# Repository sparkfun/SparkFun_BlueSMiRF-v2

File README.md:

# SparkFun BlueSMiRF v2

The [SparkFun BlueSMiRF v2](https://www.sparkfun.com/sparkfun-bluesmirf-v2.html), [SparkFun BlueSMiRF v2 - Headers](https://www.sparkfun.com/sparkfun-bluesmirf-v2-headers.html), and [SparkFun BlueSMiRF v2 - JST](https://www.sparkfun.com/sparkfun-bluesmirf-v2-jst.html) are wireless Bluetooth® serial links. These boards work as a wireless serial UART pipe and are a great wireless replacement for serial cables. Simply pair, connect, and transmit serial data between your TX/RX lines! Any serial stream from 2400 to 921600 baud can be passed seamlessly between two devices.

Duplex transmissions up to 921600bps are supported. What does this mean? You can throw a book at each BlueSMiRF, which will correctly buffer, transmit, and deliver the data streams, byte perfect, to both radios.

BlueSMiRF v2 has a multitude of exciting improvements over the original. The BlueSMiRF pinout is the same as previous Bluetooth Mates and USB-to-serial converters (i.e., FTDI, CH340, etc.), making it extremely easy to hook up to many common Arduino development boards and GNSS breakout boards.  The board can be connected directly with an Arduino Pro, Pro Mini, or any board with a standard 6-pin serial connector. We broke out the pins to the 1x6 header for this version of the board. You'll need to either solder a 1x6 female header or striped wires to the PTHs before being able to connect to another device. The SparkFun BlueSMiRF v2 is perfect for short-range applications up to 100ft (33m) indoors that require easy to setup, point-to-point communication.

A BlueSMiRF can be connected to a phone or computer to view data or remote control easily. Two BlueSMiRFs can also be easily connected using the onboard PAIR button. If needed, this button can be disabled by cutting the jumper on the back of the board.

We've designed the BlueSMiRF to be remotely configured from a phone using a serial terminal app. Changing the settings, such as the baud rate, flow control, and LED mode, is easily done using the simple AT command set. Additionally, Over The Air (OTA) updates using WiFi allow easy in-field firmware updates as new features are released.

The BlueSMiRF v2 has an on-board voltage regulator to power between 3.3V and 5V. Logic level shifting circuitry is included on all pins to be 3.3V to 5V tolerant. Note that you will need an RS232 to TTL converter for higher voltages. A jumper on the top of the board is also included to bypass the voltage regulator. Two built-in LEDs indicate when the BlueSMiRF is connected and when there is serial UART traffic.

> [!NOTE]
> Bluetooth® classic (Serial Port Profile or SPP) is primarily supported. This Bluetooth protocol is supported on Android phones, most desktops, and laptops. BlueSMiRF also supports the BLE protocol, available on all Apple phones.

This repo houses the [BlueSMiRF v2 Hookup Guide](https://docs.sparkfun.com/SparkFun_BlueSMiRF-v2) and the firmware that runs on the SparkFun BlueSMiRF v2 product line including:

- [SparkFun BlueSMiRF v2 - PTH Pins](https://www.sparkfun.com/sparkfun-bluesmirf-v2.html)
- [SparkFun BlueSMiRF v2 - Male Header Pins](https://www.sparkfun.com/sparkfun-bluesmirf-v2-headers.html)
- [SparkFun BlueSMiRF v2 - JST-GH Connector](https://www.sparkfun.com/sparkfun-bluesmirf-v2-jst.html)

> [!NOTE]
> For compiled binaries of the firmware, please see [SparkFun BlueSMiRF ESP32 Firmware Binaries](https://github.com/sparkfun/SparkFun_BlueSMiRF-v2_Binaries).

## Documentation

- **[Hookup Guide](http://docs.sparkfun.com/SparkFun_BlueSMiRF-v2/)** - Hookup guide for the BlueSMiRF v2 hosted by GitHub pages.<br>
   <br>
  *Need to download or print our hookup guide?*

  - [Print *(Print to PDF)* from Single-Page View](http://docs.sparkfun.com/SparkFun_BlueSMiRF-v2/print_view)

- **[Firmware Binaries](https://github.com/sparkfun/SparkFun_BlueSMiRF-v2_Binaries)** - Compiled binaries of the firmware on the BlueSMiRF v2

## Repository

### Contents

- **[/.github/workflows](/.github/workflows)** - YAML files used for GitHub Actions; compiles firmware binaries and deploys product documentation
- **[/docs](/docs/)** - Online documentation files
  - [/assets](/docs/assets/) - Assets files
    - [/3d_model](/docs/assets/3d_model/) - 3D models for the board
    - [/board_files](/docs/assets/board_files/) - Design files for the board
      - [KiCad Design Files](/docs/assets/board_files/kicad_files.zip) (.zip)
      - [Schematics](/docs/assets/board_files/schematics.pdf) (.pdf)
      - [Dimensions](/docs/assets/board_files/dimensions.pdf) (.pdf)
    - [/component_documentation](/docs/assets/component_documentation/) - Datasheets for hardware components
    - [/img/hookup_guide](/docs/assets/img/hookup_guide/) - Images for hookup guide documentation - Hookup guide images for the board
- **[/Firmware](/Firmware/)** - Source code for SparkFun BlueSMiRF firmware as well as various feature unit tests
- /Hardware - Hardware design files (.brd, .sch)
  - /Production - Production files

### Branch Structure
This repository has two long-term branches: `main` and `release_candidate`.

With respect to the firmware, `main` is a branch where only changes that are appropriate for all users are applied. Thus, following `main` means updating to normal releases, and perhaps bugfixes to those releases.

In contrast, `release_candidate` is where new code is added as it is developed.

The documentation source code is in `docs/` on `main`.  It is built automatically on push and stored in the branch `gh-pages`, from which it is served at the above URL. Documentation changes are pushed directly to main.

## Releases

### Firmware Releases
A release is made by merging `release_candidate` back to `main`, and then applying a tag to that commit on `main`.

A pre-release is often created using the latest stable release candidate. These binaries will have extra debug statements turned on that will not be present in a formal release, but should not affect the behavior of the firmware.

> [!NOTE]
> **Firmware Updates:** Because it's much easier to use, we recommend the OTA firmware update process. If that fails for some reason, you can upload the firmware directly. For more information, check out the tutorial under the section [Manually Reprogramming](https://docs.sparkfun.com/SparkFun_BlueSMiRF-v2/firmware-overview/#manually-reprogramming/).

### Product Variants

- [WRL-24113](https://www.sparkfun.com/sparkfun-bluesmirf-v2.html) - Initial release, PTH pads variant
- [WRL-23287](https://www.sparkfun.com/sparkfun-bluesmirf-v2-headers.html) - Initial release, male header pins variant
- [WRL-30414](https://www.sparkfun.com/sparkfun-bluesmirf-v2-jst.html) - Initial release, JST connector variant

### Version History

- [v10](https://github.com/sparkfun/SparkFun_BlueSMiRF-v2/releases/tag/v10) - Initial Release; for latest JST variant and docs landing page

## License Information
This product is ***open source***!  Please feel free to [contribute](https://docs.sparkfun.com/SparkFun_BlueSMiRF-v2/github/contribute/) to both the firmware and documentation.

Various bits of the code have different licenses applied. Anything SparkFun wrote is beerware; if you see me (or any other SparkFun employee) at the local, and you've found our code helpful, please buy us a round!

Please use, reuse, and modify these files as you see fit. Please maintain attribution to SparkFun Electronics and release anything derivative under the same license.

Distributed as-is; no warranty is given.

- Your friends at SparkFun.

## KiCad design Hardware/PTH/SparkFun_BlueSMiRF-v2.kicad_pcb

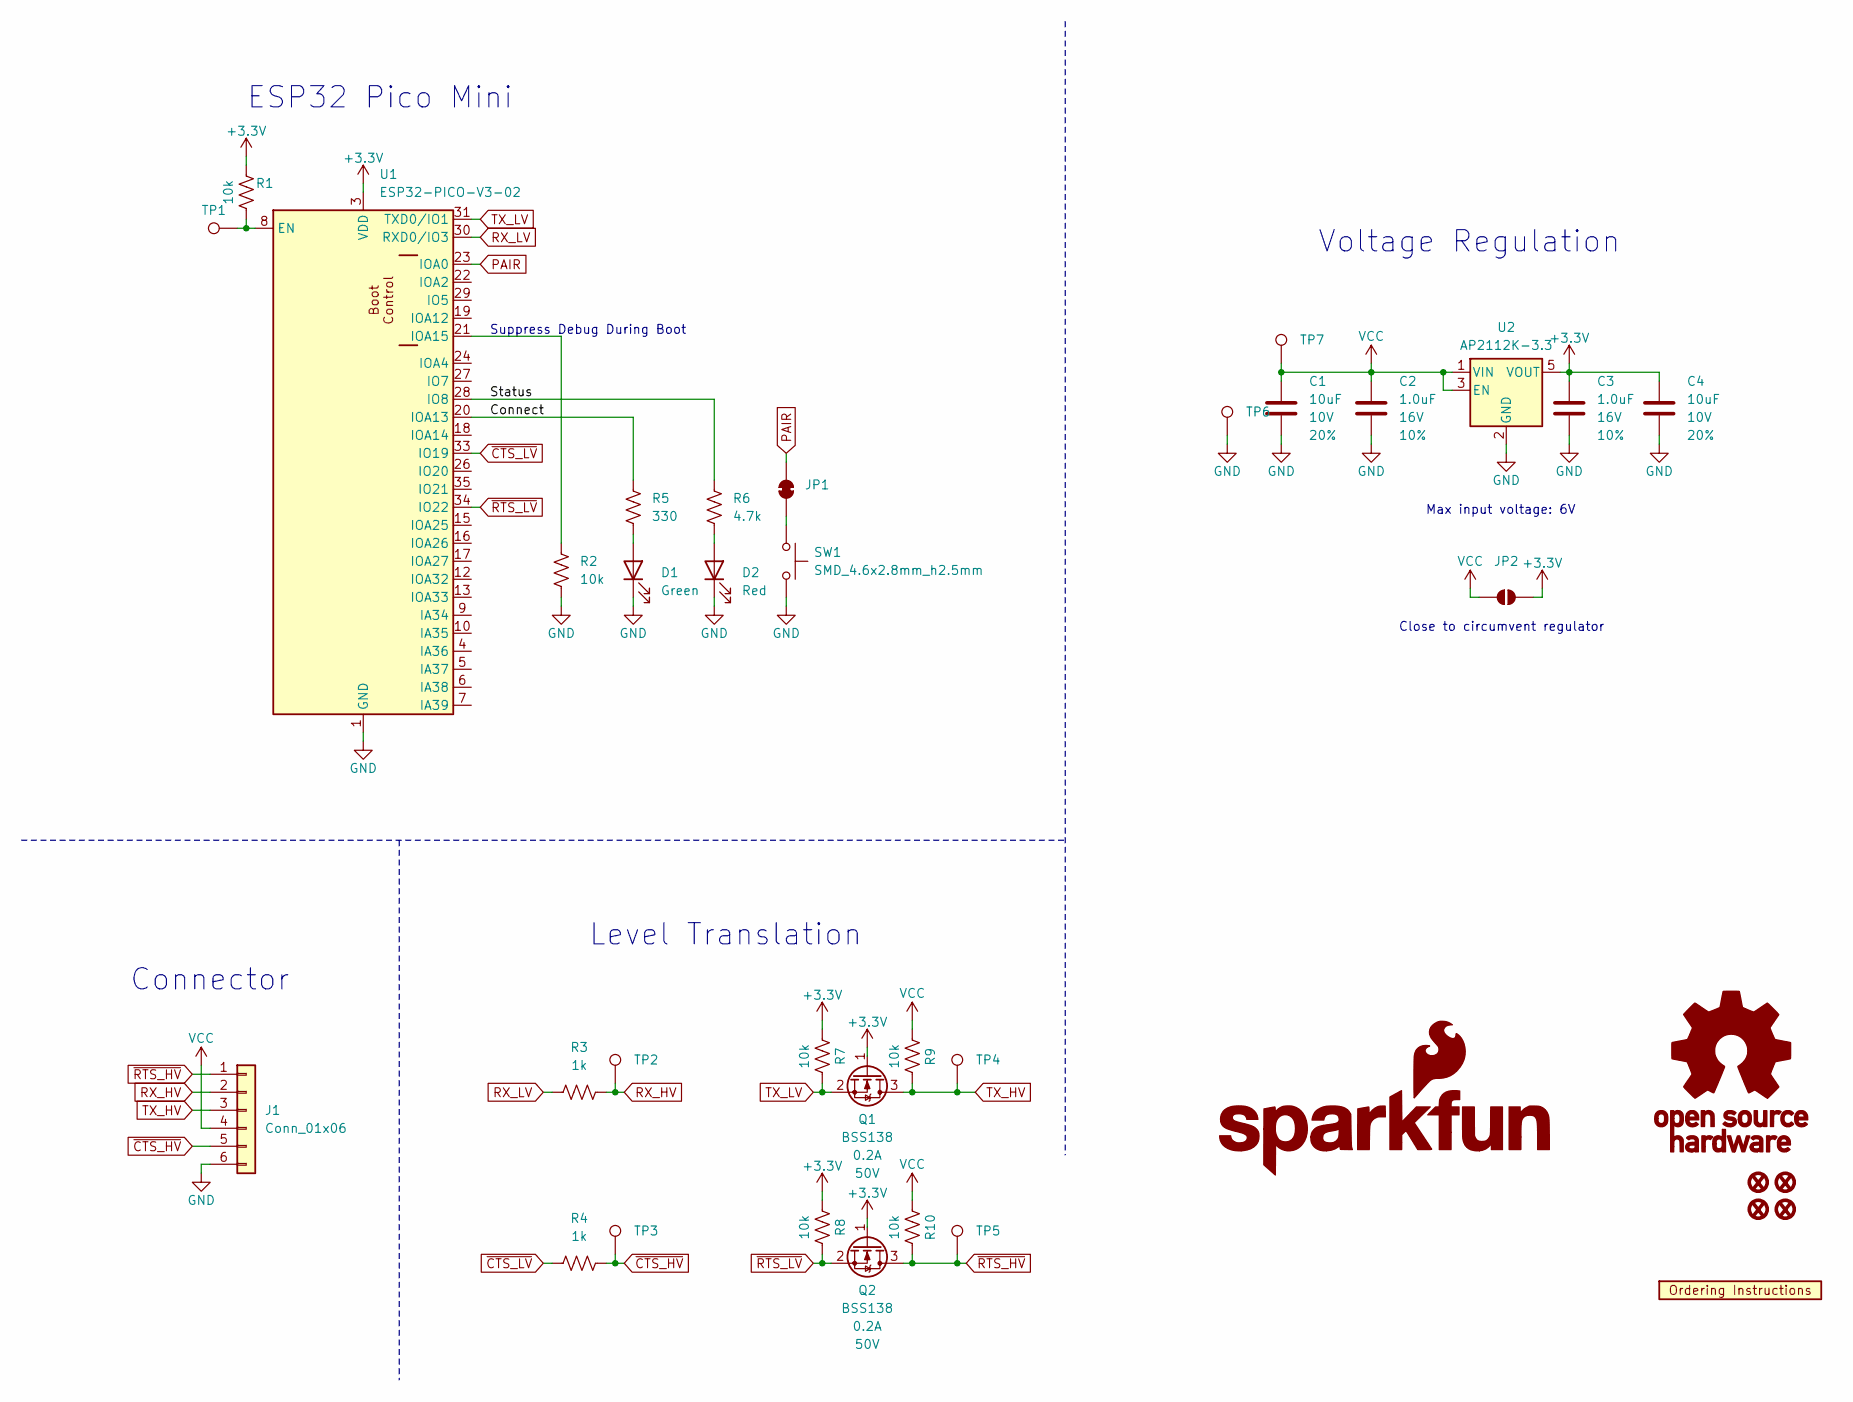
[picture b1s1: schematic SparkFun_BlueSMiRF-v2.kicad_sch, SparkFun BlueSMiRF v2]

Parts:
C1, C4: 10uF; C_0603_1608Metric; Voltage 10V; Tolerance 20%
C2, C3: 1.0uF; C_0603_1608Metric; Voltage 16V; Tolerance 10%
D1: Green; LED_0603_1608Metric_Green
D2: Red; LED_0603_1608Metric_Red
FID1, FID2, FID3, FID4: Fiducial_0.5mm; Fiducial_0.5mm_Mask1mm
G1: SparkFun_Logo
G2: OSHW_Logo; Creative_Commons_License
J1: Conn_01x06; 1x06
JP1: Jumper_2_NC_Trace
JP2: Jumper_2_NO
Q1, Q2: BSS138; SOT23-3
R1, R2, R7, R8, R9, R10: 10k; R_0603_1608Metric
R3, R4: 1k; R_0603_1608Metric
R5: 330; R_0603_1608Metric
R6: 4.7k; R_0603_1608Metric
SW1: SMD_4.6x2.8mm_h2.5mm; Push_SMD_4.6x2.8mm_h2.5mm
TP1: PTH; 1x01
TP2, TP3, TP4, TP5, TP6, TP7: 0.75mm; TestPoint-0.75mm
U1: ESP32-PICO-V3-02; ESP32-PICO-MINI
U2: AP2112K-3.3; SOT23-5
U3: Ordering_Instructions

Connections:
+3.3V: C3.1, C4.1, JP2.2 (B), Q1.1 (G), Q2.1 (G), R1.1, R7.1, R8.1, U1.3 (VDD), U2.5 (VOUT)
/Connect: R5.1, U1.20 (IOA13)
/Status: R6.1, U1.28 (IO8)
GND: C1.2, C2.2, C3.2, C4.2, D1.1 (K), D2.1 (K), J1.6, R2.2, SW1.2, TP6.1, U1.1 (GND), U1.2 (GND), U1.11 (GND), U1.14 (GND), U1.36 (GND), U1.37 (GND), U1.38 (GND), U1.39 (GND), U1.40 (GND), U1.41 (GND), U1.42 (GND), U1.43 (GND), U1.44 (GND), U1.45 (GND), U1.46 (GND), U1.47 (GND), U1.48 (GND), U1.49.1 (GND), U1.49.2 (GND), U1.49.3 (GND), U1.49.4 (GND), U1.49.5 (GND), U1.49.6 (GND), U1.49.7 (GND), U1.49.8 (GND), U1.49.9 (GND), U1.50 (GND), U1.51 (GND), U1.52 (GND), U1.53 (GND), U2.2 (GND)
unnamed: D1.2 (A), R5.2
unnamed: D2.2 (A), R6.2
unnamed: JP1.1 (A), SW1.1
unnamed: R1.2, TP1.1, U1.8 (EN)
unnamed: R2.1, U1.21 (IOA15)
PAIR: JP1.2 (B), U1.23 (IOA0)
RX_HV: J1.2, R3.2, TP2.1
RX_LV: R3.1, U1.30 (RXD0/IO3)
TX_HV: J1.3, Q1.3 (D), R9.2, TP4.1
TX_LV: Q1.2 (S), R7.2, U1.31 (TXD0/IO1)
VCC: C1.1, C2.1, J1.4, JP2.1 (A), R9.1, R10.1, TP7.1, U2.1 (VIN), U2.3 (EN)
~CTS_HV: J1.5, R4.2, TP3.1
~CTS_LV: R4.1, U1.33 (IO19)
~RTS_HV: J1.1, Q2.3 (D), R10.2, TP5.1
~RTS_LV: Q2.2 (S), R8.2, U1.34 (IO22)

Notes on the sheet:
Max input voltage: 6V
Level Translation
Voltage Regulation
ESP32 Pico Mini
Close to circumvent regulator
Connector
Suppress Debug During Boot

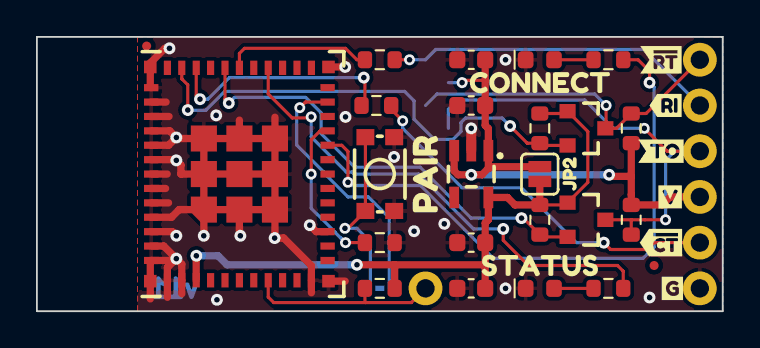
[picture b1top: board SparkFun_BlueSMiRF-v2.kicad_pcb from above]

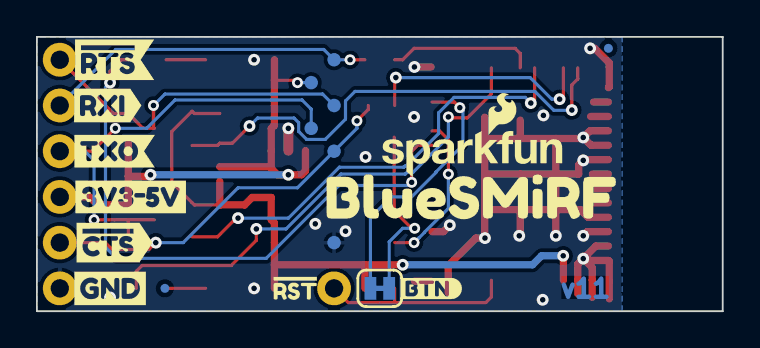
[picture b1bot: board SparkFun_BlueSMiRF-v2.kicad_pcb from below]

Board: 2 copper layers, 38.1 x 15.2 mm, 56 parts (18 on the bottom side), 19 nets.

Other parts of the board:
kibuzzard-64C47F40: G***; kibuzzard-64C47F40
kibuzzard-654D17C6: G***; kibuzzard-654D17C6
kibuzzard-654D17D1: G***; kibuzzard-654D17D1
kibuzzard-655A5C47: G***; kibuzzard-655A5C47
kibuzzard-655A43AA: G***; kibuzzard-655A43AA
kibuzzard-655A44E1: G***; kibuzzard-655A44E1
kibuzzard-655A45F8: G***; kibuzzard-655A45F8
kibuzzard-655A444A: G***; kibuzzard-655A444A
kibuzzard-655A532D: G***; kibuzzard-655A532D
kibuzzard-655A4368: G***; kibuzzard-655A4368
kibuzzard-655A4384: G***; kibuzzard-655A4384
kibuzzard-655A4397: G***; kibuzzard-655A4397
kibuzzard-655A4470: G***; kibuzzard-655A4470
kibuzzard-655A4492: G***; kibuzzard-655A4492
kibuzzard-65022EAF: G***; kibuzzard-65022EAF
kibuzzard-65022F1B: G***; kibuzzard-65022F1B
kibuzzard-6502231B: G***; kibuzzard-6502231B
kibuzzard-6502302E: G***; kibuzzard-6502302E
kibuzzard-65023040: G***; kibuzzard-65023040

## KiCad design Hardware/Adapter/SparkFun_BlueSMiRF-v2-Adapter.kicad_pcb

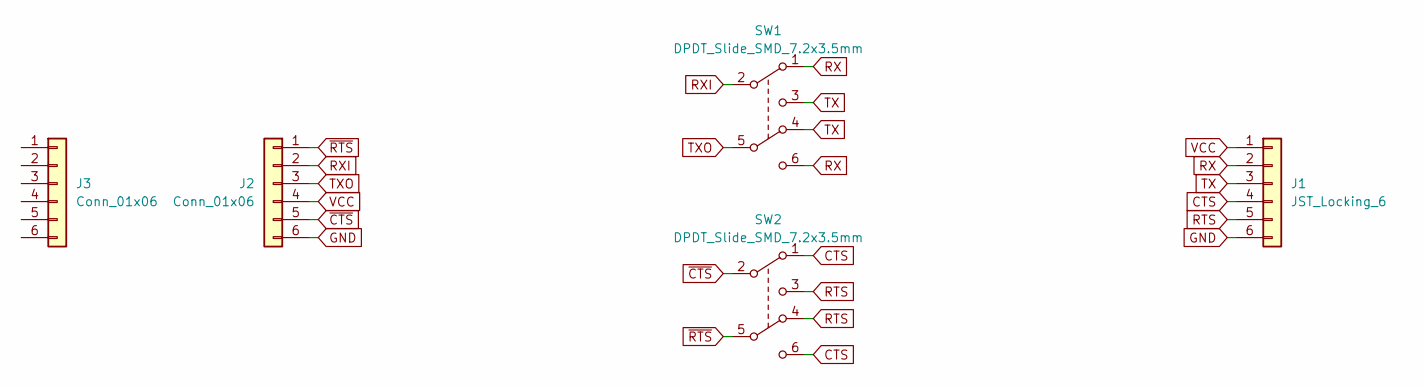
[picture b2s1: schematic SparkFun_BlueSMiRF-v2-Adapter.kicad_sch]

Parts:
J1: JST_Locking_6; JST_SMD_1.25mm-6_Locking
J2: Conn_01x06; 1x06_SMD_RA_Female
J3: Conn_01x06; 1x06_SMD_RA_Male
SW1, SW2: DPDT_Slide_SMD_7.2x3.5mm; Slide_DPDT_SMD_7.2x3.5mm; Mfg Part# ABC

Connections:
CTS: J1.4, SW2.1 (A), SW2.6 (C)
GND: J1.6, J2.6
RTS: J1.5, SW2.3 (C), SW2.4 (A)
RX: J1.2, SW1.1 (A), SW1.6 (C)
RXI: J2.2, SW1.2 (B)
TX: J1.3, SW1.3 (C), SW1.4 (A)
TXO: J2.3, SW1.5 (B)
VCC: J1.1, J2.4
~CTS: J2.5, SW2.2 (B)
~RTS: J2.1, SW2.5 (B)

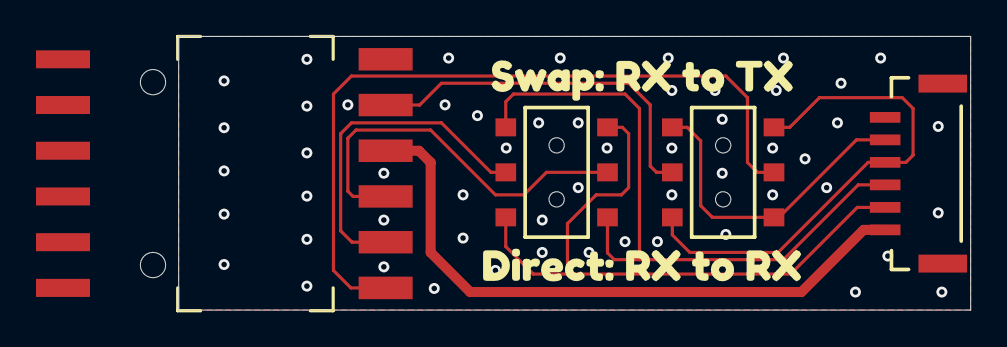
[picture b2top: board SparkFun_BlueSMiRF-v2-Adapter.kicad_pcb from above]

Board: 2 copper layers, 44.0 x 15.2 mm, 19 parts (12 on the bottom side), 10 nets.

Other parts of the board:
kibuzzard-688F9C93: G***; kibuzzard-688F9C93
kibuzzard-688F9D85: G***; kibuzzard-688F9D85
kibuzzard-688F95BB: G***; kibuzzard-688F95BB
kibuzzard-688F95E9: G***; kibuzzard-688F95E9
kibuzzard-688F95F7: G***; kibuzzard-688F95F7
kibuzzard-688F940F: G***; kibuzzard-688F940F
kibuzzard-688F9569: G***; kibuzzard-688F9569
kibuzzard-688F9588: G***; kibuzzard-688F9588
kibuzzard-6880B6B5: G***; kibuzzard-6880B6B5
kibuzzard-6880B6C0: G***; kibuzzard-6880B6C0
kibuzzard-6883FB8C: G***; kibuzzard-6883FB8C
kibuzzard-6883FB9A: G***; kibuzzard-6883FB9A
kibuzzard-6883FB93: G***; kibuzzard-6883FB93
kibuzzard-6883FBA0: G***; kibuzzard-6883FBA0

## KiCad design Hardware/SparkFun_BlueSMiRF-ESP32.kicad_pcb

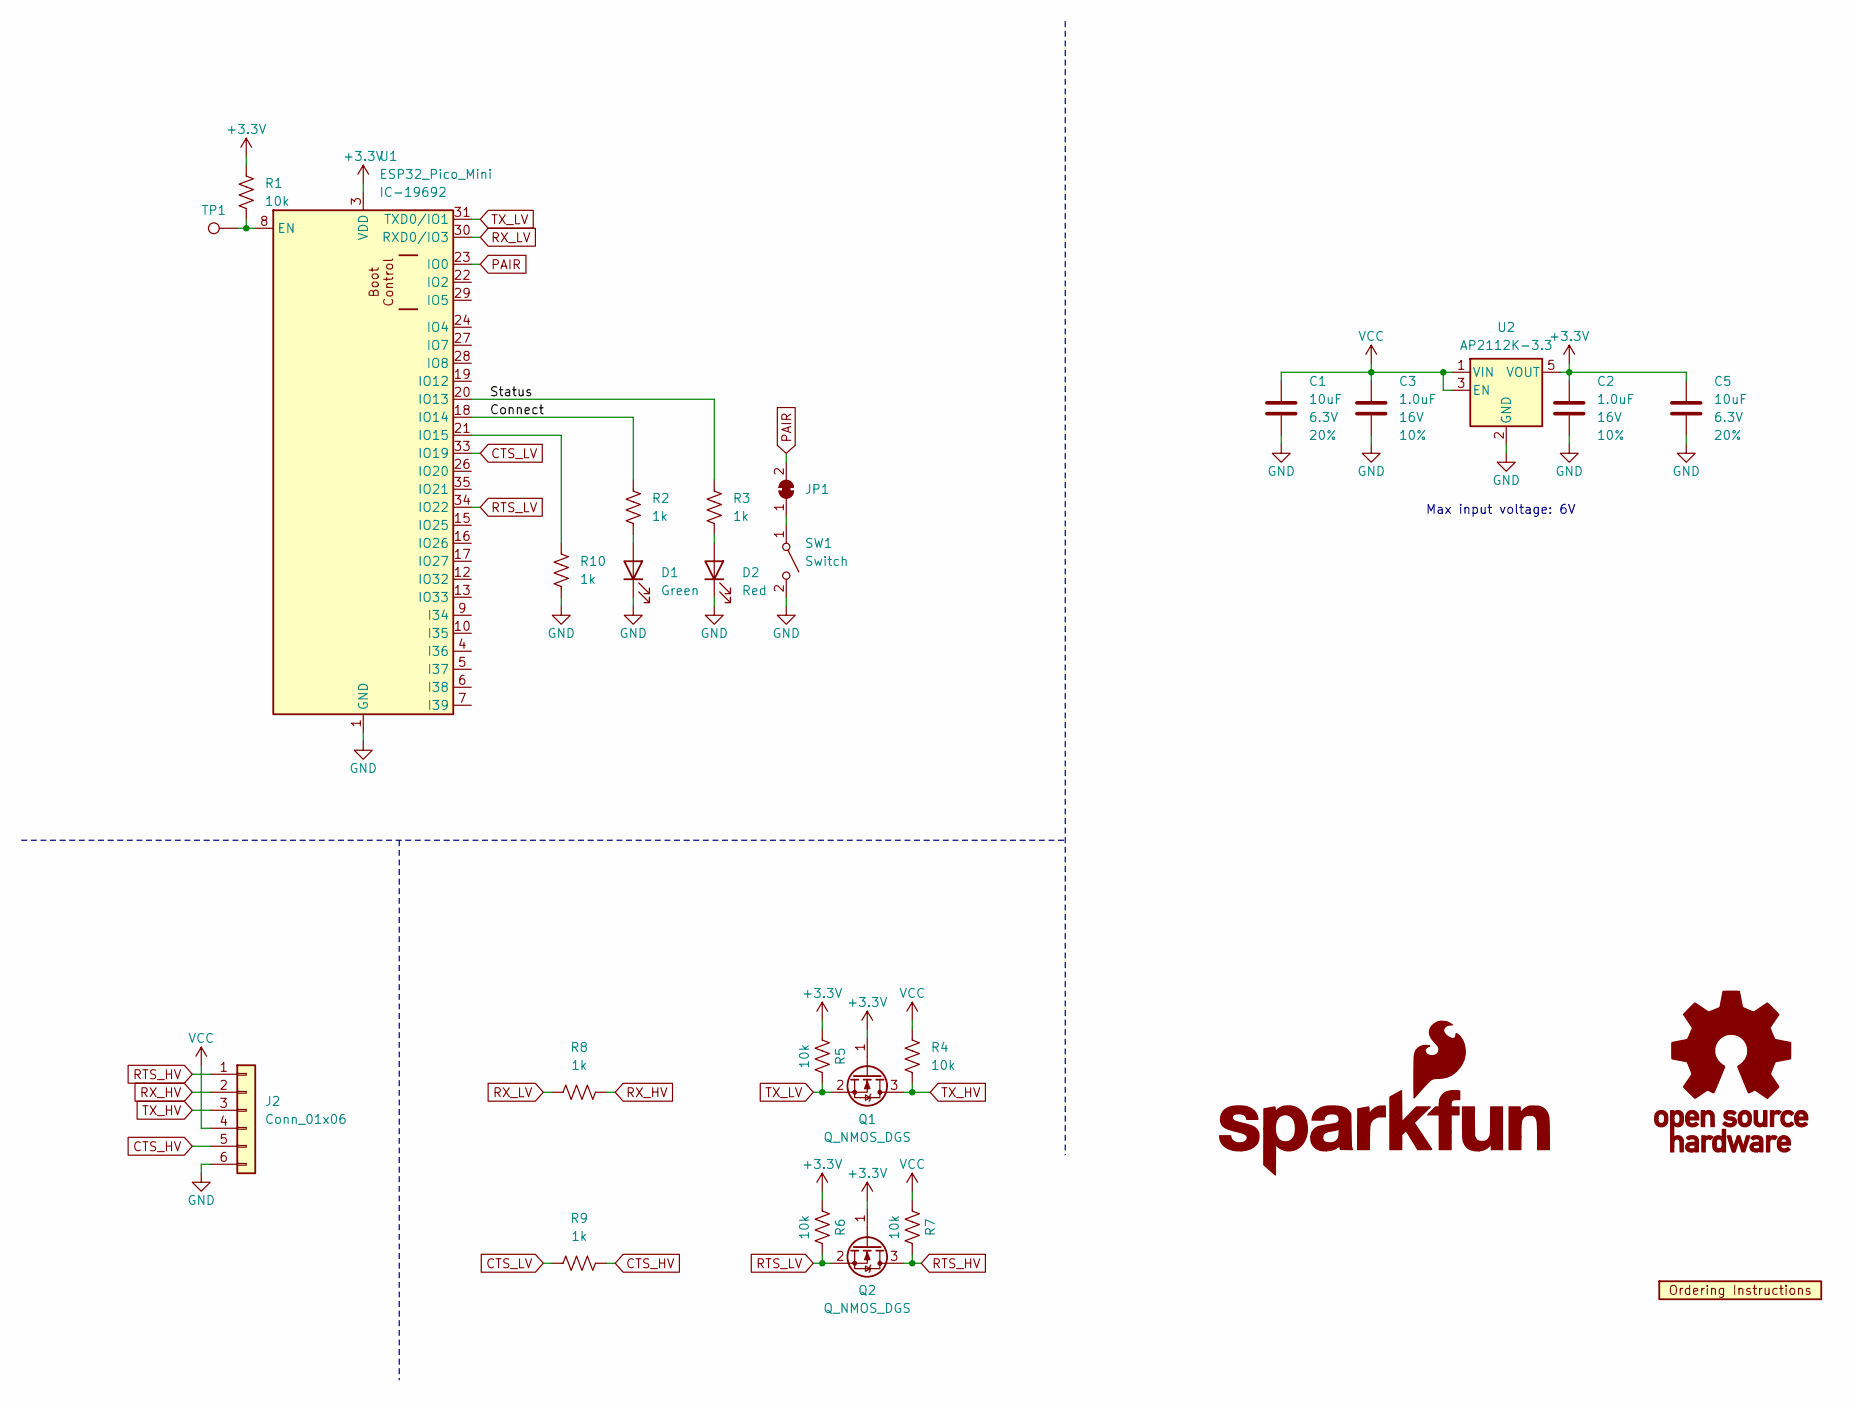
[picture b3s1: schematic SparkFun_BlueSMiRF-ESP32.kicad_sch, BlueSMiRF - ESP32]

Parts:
C1, C5: 10uF; C_0603_1608Metric; Voltage 6.3V; Tolerance 20%
C2, C3: 1.0uF; C_0603_1608Metric; Voltage 16V; Tolerance 10%
D1: Green; LED_0603_1608Metric
D2: Red; LED_0603_1608Metric
G1: SparkFun_Logo
G2: OSHW_Logo; Creative_Commons_License
J2: Conn_01x06; 1X06-SMD_RA_MALE
JP1: SMT-JUMPER_2_NC_TRACE_NO-SILK
Q1, Q2: Q_NMOS_DGS; SOT23-3
R1, R4, R5, R6, R7: 10k; R_0603_1608Metric
R2, R3, R8, R9, R10: 1k; R_0603_1608Metric
SW1: Switch; Momentary_SMD_4.6x2.8mm
TP1: TestPoint; 1X01
U1: ESP32_Pico_Mini; ESP32-MINI
U2: AP2112K-3.3; SOT23-5
U3: Ordering_Instructions

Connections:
+3.3V: C2.1, C5.1, Q1.1 (G), Q2.1 (G), R1.1, R5.1, R6.1, U1.3 (VDD), U2.5 (VOUT)
/Connect: R2.1, U1.18 (IO14)
/Status: R3.1, U1.20 (IO13)
CTS_HV: J2.5, R9.2
CTS_LV: R9.1, U1.33 (IO19)
GND: C1.2, C2.2, C3.2, C5.2, D1.1 (K), D2.1 (K), J2.6, R10.2, SW1.2 (B), U1.1 (GND), U1.2 (GND), U1.11 (GND), U1.14 (GND), U1.36 (GND), U1.37 (GND), U1.38 (GND), U1.39 (GND), U1.40 (GND), U1.41 (GND), U1.42 (GND), U1.43 (GND), U1.44 (GND), U1.45 (GND), U1.46 (GND), U1.47 (GND), U1.48 (GND), U1.49.1 (GND), U1.49.2 (GND), U1.49.3 (GND), U1.49.4 (GND), U1.49.5 (GND), U1.49.6 (GND), U1.49.7 (GND), U1.49.8 (GND), U1.49.9 (GND), U1.50 (GND), U1.51 (GND), U1.52 (GND), U1.53 (GND), U2.2 (GND)
unnamed: D1.2 (A), R2.2
unnamed: D2.2 (A), R3.2
unnamed: JP1.1 (A), SW1.1 (A)
unnamed: R1.2, TP1.1, U1.8 (EN)
unnamed: R10.1, U1.21 (IO15)
PAIR: JP1.2 (B), U1.23 (IO0)
RTS_HV: J2.1, Q2.3 (D), R7.2
RTS_LV: Q2.2 (S), R6.2, U1.34 (IO22)
RX_HV: J2.2, R8.2
RX_LV: R8.1, U1.30 (RXD0/IO3)
TX_HV: J2.3, Q1.3 (D), R4.2
TX_LV: Q1.2 (S), R5.2, U1.31 (TXD0/IO1)
VCC: C1.1, C3.1, J2.4, R4.1, R7.1, U2.1 (VIN), U2.3 (EN)

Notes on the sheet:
Max input voltage: 6V

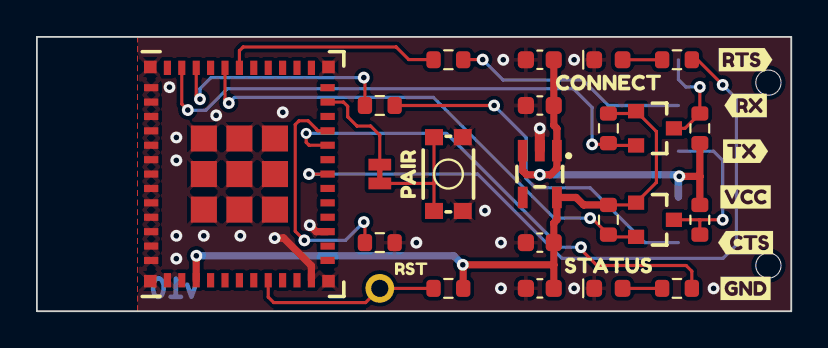
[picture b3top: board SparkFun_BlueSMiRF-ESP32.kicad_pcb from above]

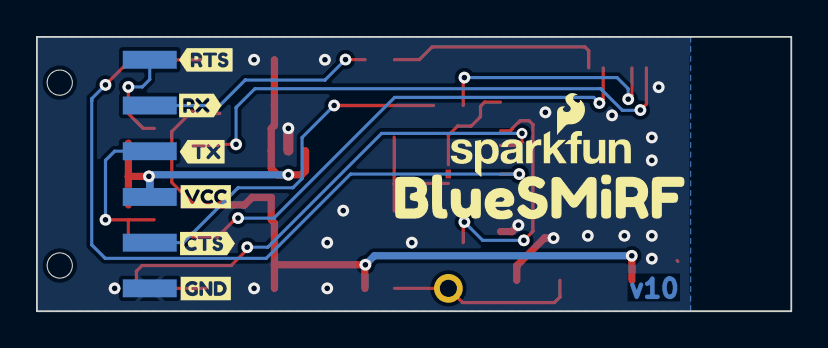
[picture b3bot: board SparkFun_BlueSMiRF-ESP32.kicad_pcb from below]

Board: 2 copper layers, 41.9 x 15.2 mm, 43 parts (8 on the bottom side), 19 nets.

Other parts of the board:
kibuzzard-64C47E8F: G***; kibuzzard-64C47E8F
kibuzzard-64C47E89: G***; kibuzzard-64C47E89
kibuzzard-64C47F40: G***; kibuzzard-64C47F40
kibuzzard-64C483A5: G***; kibuzzard-64C483A5
kibuzzard-64C483E5: G***; kibuzzard-64C483E5
kibuzzard-64C484A1: G***; kibuzzard-64C484A1
kibuzzard-64C484B8: G***; kibuzzard-64C484B8
kibuzzard-64C4837C: G***; kibuzzard-64C4837C
kibuzzard-64C4844B: G***; kibuzzard-64C4844B
kibuzzard-64C4846C: G***; kibuzzard-64C4846C
kibuzzard-64C48117: G***; kibuzzard-64C48117
kibuzzard-64C48159: G***; kibuzzard-64C48159
kibuzzard-64C48347: G***; kibuzzard-64C48347
kibuzzard-64C48410: G***; kibuzzard-64C48410
kibuzzard-64C48455: G***; kibuzzard-64C48455
kibuzzard-64C48496: G***; kibuzzard-64C48496
kibuzzard-64C48505: G***; kibuzzard-64C48505

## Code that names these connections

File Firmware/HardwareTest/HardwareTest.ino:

/*
*/

uint8_t pin_pair = 0;
uint8_t pin_cts = 19;
uint8_t pin_rts = 22;
uint8_t pin_statusLED = 8;
uint8_t pin_connectLED = 13;

unsigned long lastChange = 0;

void setup()
{
  Serial.begin(115200); // Start serial for any initial debug messages

  pinMode(pin_pair, INPUT_PULLUP);

  pinMode(pin_cts, INPUT); //Has external pullup

  pinMode(pin_rts, OUTPUT);
  digitalWrite(pin_rts, LOW);

  pinMode(pin_statusLED, OUTPUT);
  digitalWrite(pin_statusLED, LOW);

  pinMode(pin_connectLED, OUTPUT);
  digitalWrite(pin_connectLED, HIGH);
}

void loop()
{
  Serial.println("Running");
  
  if (millis() - lastChange > 1000)
  {
    lastChange = millis();
    digitalWrite(pin_statusLED, !digitalRead(pin_statusLED));
    digitalWrite(pin_connectLED, !digitalRead(pin_connectLED));
    digitalWrite(pin_rts, !digitalRead(pin_rts));
  }

  if (digitalRead(pin_cts) == LOW)
    Serial.println("CTS pressed!");

  if (digitalRead(pin_pair) == LOW)
    Serial.println("Pair pressed!");

  delay(100);

}

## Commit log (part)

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2023-07-31 Ignore backups
2023-08-08 Rename files
2023-08-10 Update panel with PROD_IDs.
2023-08-10 Update PROD_IDs
2023-08-10 Update panel files
2023-11-09 Add PTH variant
2023-11-14 Add test sketches
2023-11-14 Add initial firmware
2023-11-15 Add custom partition file
2023-11-15 Fix example
2023-11-15 Update Arduino CLI commands
2023-11-15 Create github workflow for compilation
2023-11-15 Typo fix
2023-11-16 Add custom BluetoothSerial library
2023-11-17 Remove old BT library
2023-11-17 Add debug print
2023-11-17 Decrease btTxSize default to 512 * 2.
2023-11-17 Reduce default buffer to allow discovery.
2023-11-19 Post design review fixes.
2023-11-19 Add PTH panel files
2023-11-20 Apply design review changes to PTH version.
2023-11-22 Fix printing of escape char during normal serial operations
2023-11-22 Fix flush when not connected to BT
2023-11-22 Increase task sizes to handle WiFi during commands
2023-11-22 Move to systemPrints
2023-11-22 Expose BT state even if not compiled
2023-11-22 Add WiFi OTA
2023-11-22 Remove flush before restart
2023-11-22 Add WiFi library
2023-11-22 Increase version to 99 to allow local compile trigers
2023-11-22 Remove developer switch
2023-11-22 Add print version command
2023-12-14 Update pins to match v10 hardware.
2023-12-14 Update comments. Add ledUpdate.
2023-12-14 Add LED behavior comments
2023-12-14 Remove Serial.prints
2023-12-14 Error to ATC if WiFi not compiled
2023-12-14 Use PIN_UNDEFINED
2023-12-14 Fix workflow
2023-12-14 Disable remote BT config by default.
2023-12-14 Add OTA lib.
2023-12-14 Add max command time
2023-12-14 Default the device nick name if one is not given.
2023-12-14 Change BSS138 resistors to 10k
2023-12-21 Add button pairing, MAC command pairing, and LED modes
2023-12-21 Fix setting size check.
2023-12-21 Flush serial to avoid initial printing corruptions
2023-12-21 Add Bluetooth connect by name.
2023-12-21 Add connect via Friendly Name. Fix LED behavior.
2023-12-21 Limit LED fade brightness.
2023-12-22 Suppress printing in command mode. Fix txBuffer wrap around.
2023-12-22 Remove compile guards
2023-12-22 Fix WiFi call to Bluetooth
2023-12-26 Rename inLocalCommandMode variable
2023-12-26 Rename remoteEscapeCharsReceived
2023-12-26 Add support for remote config
2023-12-26 Add PSRAM support
2023-12-26 Allow WiFi update during BT connection.
2023-12-26 Add token support for hidden repo
2023-12-26 Add JSON update to workflow
2023-12-26 Update readme. Delete old files.
2023-12-26 Add detect for dev hardware
2024-01-03 Re-order settings in alphabetical order.
2024-01-03 Change OTA check to use major.minor.
2024-01-03 Prelim docs
2024-01-03 Rename to BlueSMiRF v2.
2024-01-03 Rename to BlueSMiRF-v2
2024-01-03 Rename directory to BlueSMiRF-v2
2024-01-06 Update JSON URL for OTA
2024-01-08 Rename Design Files
    - The SMD is actually the one with the headers. =) Renaming files to reflect the boards with headers.
2024-01-08 Increase setting length var size
2024-01-08 Turn on warnings
2024-01-08 Catch invalid radio setting
2024-01-08 Correct errors during more stringent compilation
2024-01-08 Increase task sizes to allow BLE
2024-01-08 Add debug prints for unimplemented functions
2024-01-09 Fix broadcast names during pairing steps
2024-01-09 Control both LEDs during button events
2024-01-10 Add -BLE to broadcast name during BLE mode
2024-01-10 Add bT radio start and rename.
2024-01-10 Add BLE connected().
2024-01-10 Exit button pairing if in BLE mode.
2024-01-10 Limit Bluetooth nicknames to 28 chars
2024-01-10 Exit pairing mode in BLE mode.
2024-01-10 Favor connect LED in dev hardware.
2024-01-10 Add compiler warnings and all for different task options.
2024-01-10 Reduce broadcast names to 50 bytes
2024-01-10 Change device search to allow MAC in string
2024-01-10 Set name during pairing (without nick)
2024-01-10 Allow Status LED to blink during pairing hold
2024-01-10 Enable MAC/Name connect.
2024-01-10 Rename devices after successful paired connection
2024-01-10 Enable PSRAM in workflow
2024-01-11 Update version to v10
2024-01-11 Increase version
2024-01-23 Pushing Hookup Guide for Launch
2024-01-23 Minor Changes
2024-01-24 Add notes and extra details
2024-01-25 Fix file name
2024-01-25 Allow larger buffer size entry.
2024-01-25 Increase buffer size defaults.
2024-01-25 Fix a few typos.
2024-01-25 Camel case v2.
2024-01-26 Add Product Showcase
2024-01-26 Docs: Add right angle headers to Proto Accessories
2024-01-26 Fix v2 camelcase.
2024-01-30 Code block fix
    Enables word/line wrap in code blocks
2024-02-01 Deployed d7d6e83 with MkDocs version: 1.5.3
2024-08-17 Add 3D models
2024-08-19 Revert "Add 3D models"
    This reverts commit f06ec004f059f8b2f723d6c27b798dd6a6ac20d5.
2024-10-29 Deployed 6a87f1e with MkDocs version: 1.6.1
2024-11-15 Update 3D models and components to current library
2024-11-15 Update to use current SparkFun KiCad library
2024-11-15 Fixing switch
2024-11-15 Update Copy KiCad Files
    Update Copy KiCad Files for Product Page & Tutorial so packages with 3D models are up-to-date.
2024-11-15 Remove STL File
2024-11-15 Deployed b647a5f with MkDocs version: 1.6.1
2024-12-10 Deployed 2c08c21 with MkDocs version: 1.6.1
2025-03-28 Update bluetoothSelect.h
    copy of file from rtkeverywhere
2025-03-28 Update Bluetooth.ino
    Copied file from rtkEverywhere
2025-03-28 Updated versions taken from rtk Everywhere
2025-06-29 Update at_commands.md - replace escape character
2025-06-29 Deployed 8b4b997 with MkDocs version: 1.6.1
2025-07-25 JST connector variant
    Add JST connector version that would be compatible with the JST cables used for the telemetry radios
2025-07-25 JST adapter w/ headers
    An adapter with a JST connector and female header, which would be compatible with the JST cables used for the telemetry radios
2025-08-20 Make backwards compatible
    Earlier boards had RX and TX lines swapped
    - Adds switches on RX/TX lines
2025-09-10 Remove files
    Deleted VSCode config files
    Removed unused toc-backup.html
2025-09-10 Replace <center> tag
    Replaced deprecated <center> tags with <article> elements and inline styles for better HTML5 compliance
2025-09-10 Update introduction.md
    Standardized indentation and removed unnecessary HTML comments
2025-09-10 Update navigation and tabs for print view and branding
    Revised navigation and tab labels to use '🖨️ Print View' instead of 'Hard Copies' and updated the logo/title section for improved branding. Also cleaned up the single-page view button markup in main.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
2025-09-10 Update copyright year to 2025 and revise license
    Updated the copyright year to 2025 in both LICENSE.md and mkdocs.yml. Also revised the MIT license text in LICENSE.md for clarity and updated the SparkFun copyright notice.
2025-09-10 Update logo references and favicon path in docs
    Renamed the favicon image and updated its path in mkdocs.yml. Removed an unused small logo image and changed icon references from 'sfe-logo' to 'sfe' for consistency.
2025-09-10 Add custom header, social, and copyright partials
    Introduces custom Jinja2 partials for header, social links, copyright, and generator to the MkDocs theme. Updates mkdocs.yml to adjust social icons, add a generator position option, and remove the co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
2025-09-10 Add custom icons and update MkDocs configuration
    Added multiple SVG branding logos to overrides/.icons and a README for icon usage. Updated mkdocs.yml to enhance theme customization, navigation, plugins, and markdown extensions, including support f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
2025-09-10 Refactor and enhance documentation build workflow
    Renamed the workflow file to 'build_documentation.yml' and updated the workflow name to 'Build Documentation'. Improved the workflow by adding submodule update steps, fixing a typo in the install ste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
2025-09-10 Deployed 351fc27 with MkDocs version: 1.6.1
2025-12-05 Update/Add Page Details
    Add project details
    - Company
    - Project Name
    - Designer
    - Revision #
2025-12-05 Design Update
    Update symbols and footprints based on latest SparkFun library
    Extended board length to line up with grid layout: 1.5" -> 1.6"
2025-12-05 Update PCB
    - Move fiducial location
    - Add ground via
2025-12-05 Change version text
2025-12-09 Remove temp file
2025-12-09 Add production files
    From cammer, panelizer, and BOM plug-ins
2025-12-09 Deployed 7658ddf with MkDocs version: 1.6.1
2026-03-24 Add design files
    Adds and links the design files for JST variant
2026-03-24 Remove `hard_copy.md` file
    Removes `hard_copy.md` file
    Reworks links to the `single_page.md` file instead
2026-03-24 Update site configuration
    Updates CSS styling, configurations, javascript, layout, etc.
2026-03-24 Update GitHub instructions
    Updates instructions for GitHub issues and contributions
2026-03-24 Replace relative docs links
2026-03-26 Fix styling and images
    Replaces HTML with Markdown
    - Replaces table use for images
    - Uses absolute links to image files
    - Removes hard-coded styling
2026-04-02 Fix docs
    Fixes
    - Bad links
    - Missing alt text
    - Rename files
    - shorten file names on images
    - consistent nomenclature
2026-04-02 Add JST variant
    Add JST variant
    Update product links
    Add design files section
    - Reconfigure file directory for board files
2026-04-02 Deployed 3007a59 with MkDocs version: 1.6.1
2026-04-02 Update build workflow
    Adjusts for deprecation of mkdocs-material
2026-04-02 Deployed f704cd2 with MkDocs version: 1.6.1
2026-04-04 Fix board files
    Removes ordering instructions from JST dimensions file
2026-04-04 Update Commands.ino
    Adds exit from Bluetooth command mode for ATX command
2026-04-04 Fixes 3D model rendering
    Fixes material index
2026-04-04 Adds banner images
    Adds banner images to readme and hookup guide
2026-04-04 Create composite files
    Combines the product design PDF files
2026-06-03 Deployed 95392ae with MkDocs version: 1.6.1

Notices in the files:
parts and their libraries:
https://creativecommons.org/licenses/by-sa/4.0
Released under the Creative Commons Attribution Share-Alike 4.0 License
